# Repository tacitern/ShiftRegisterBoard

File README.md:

# ShiftRegisterBoard
This project uses 8 8bit shift registers to produce 8 data independent bar graphs

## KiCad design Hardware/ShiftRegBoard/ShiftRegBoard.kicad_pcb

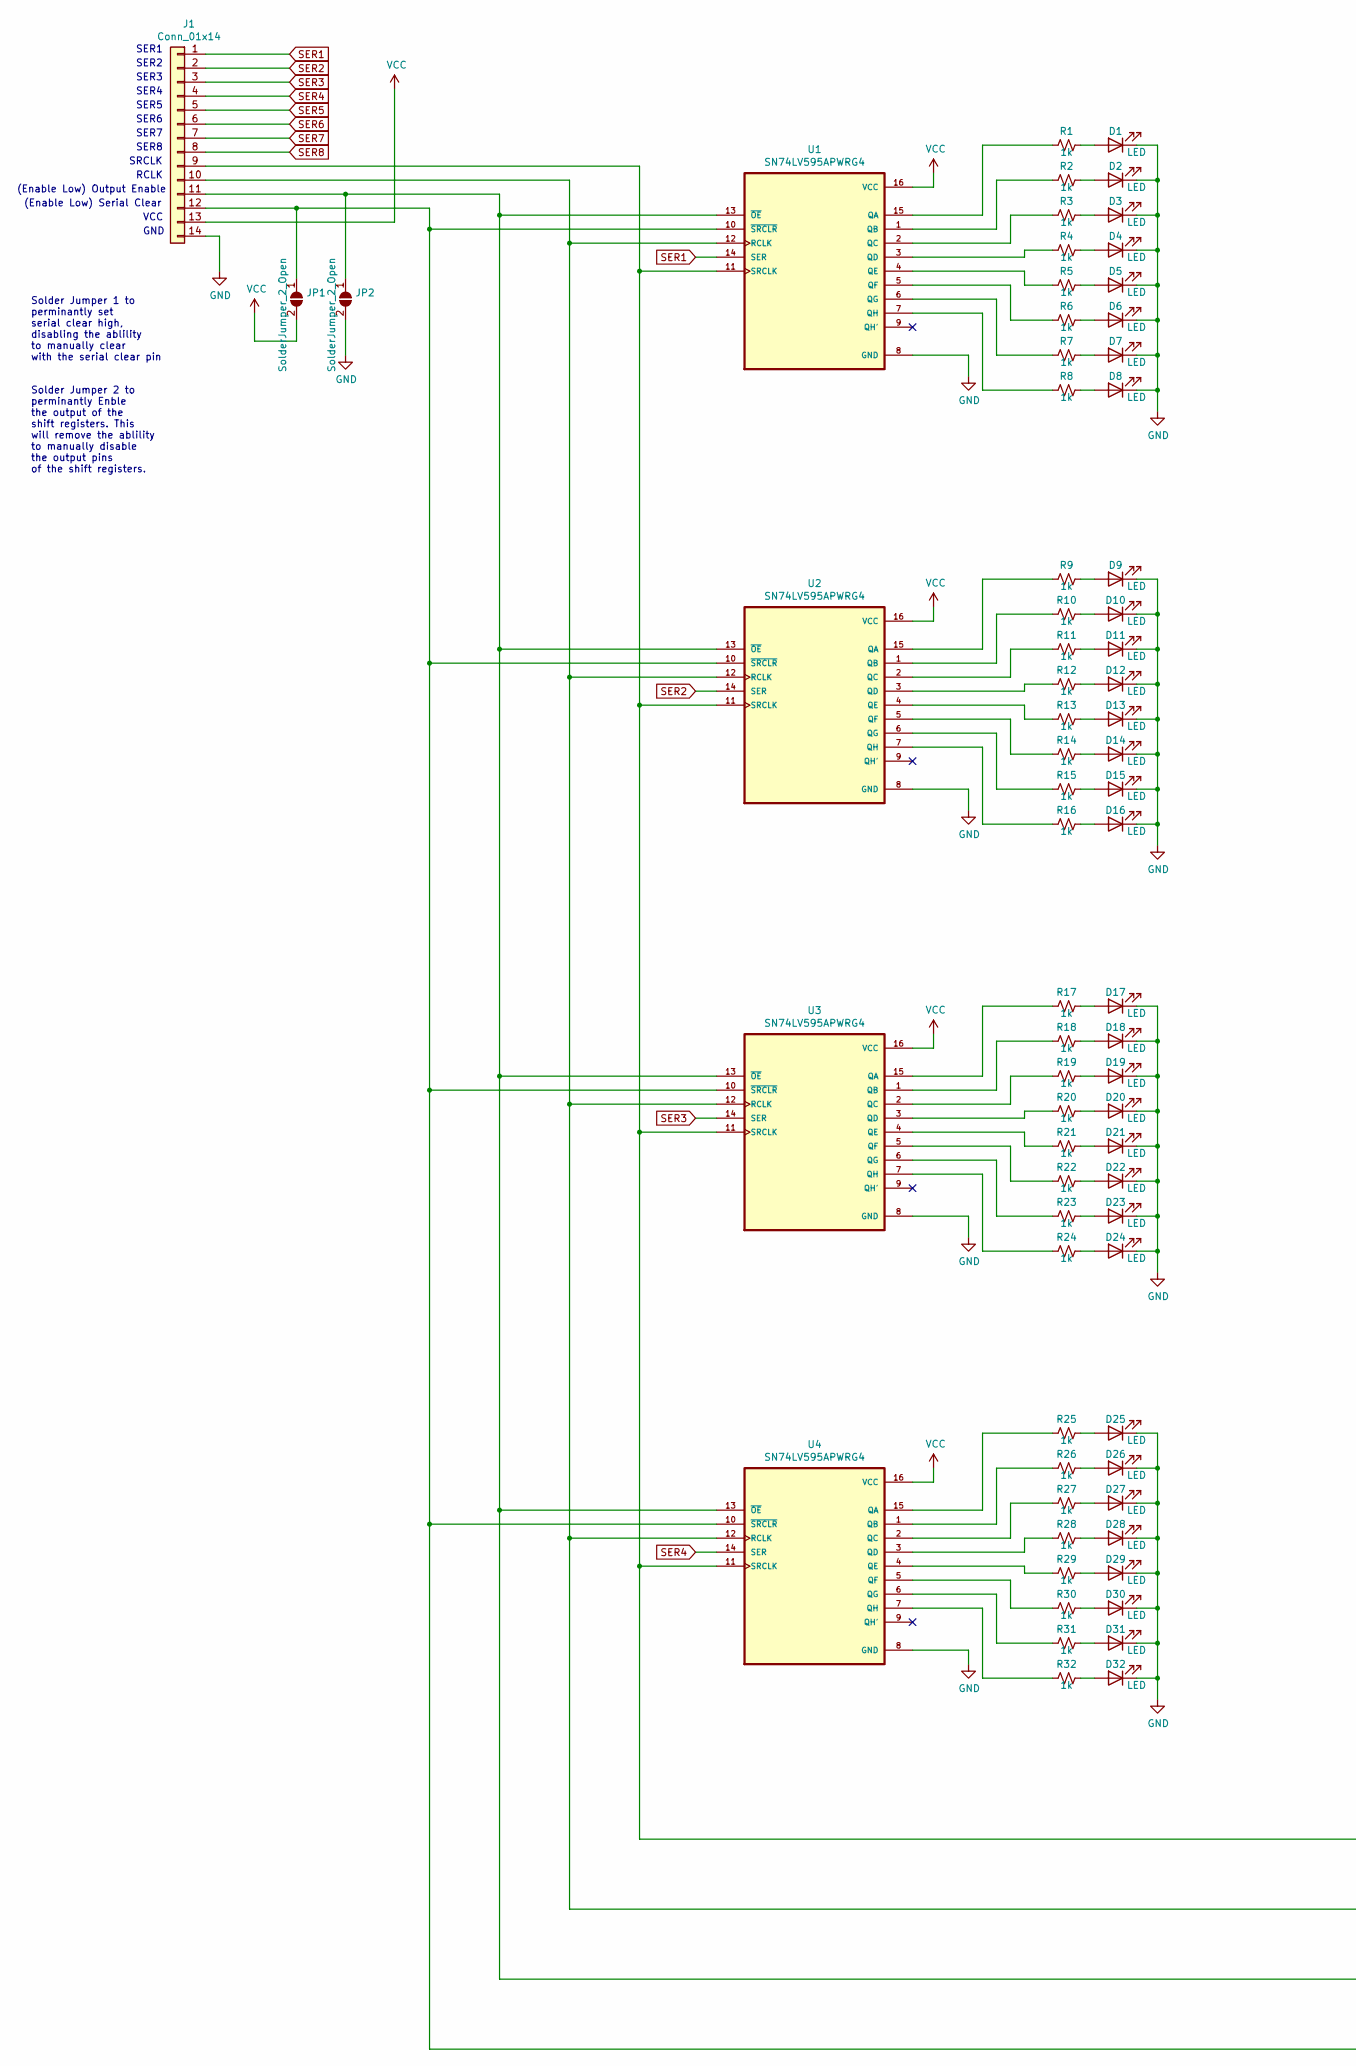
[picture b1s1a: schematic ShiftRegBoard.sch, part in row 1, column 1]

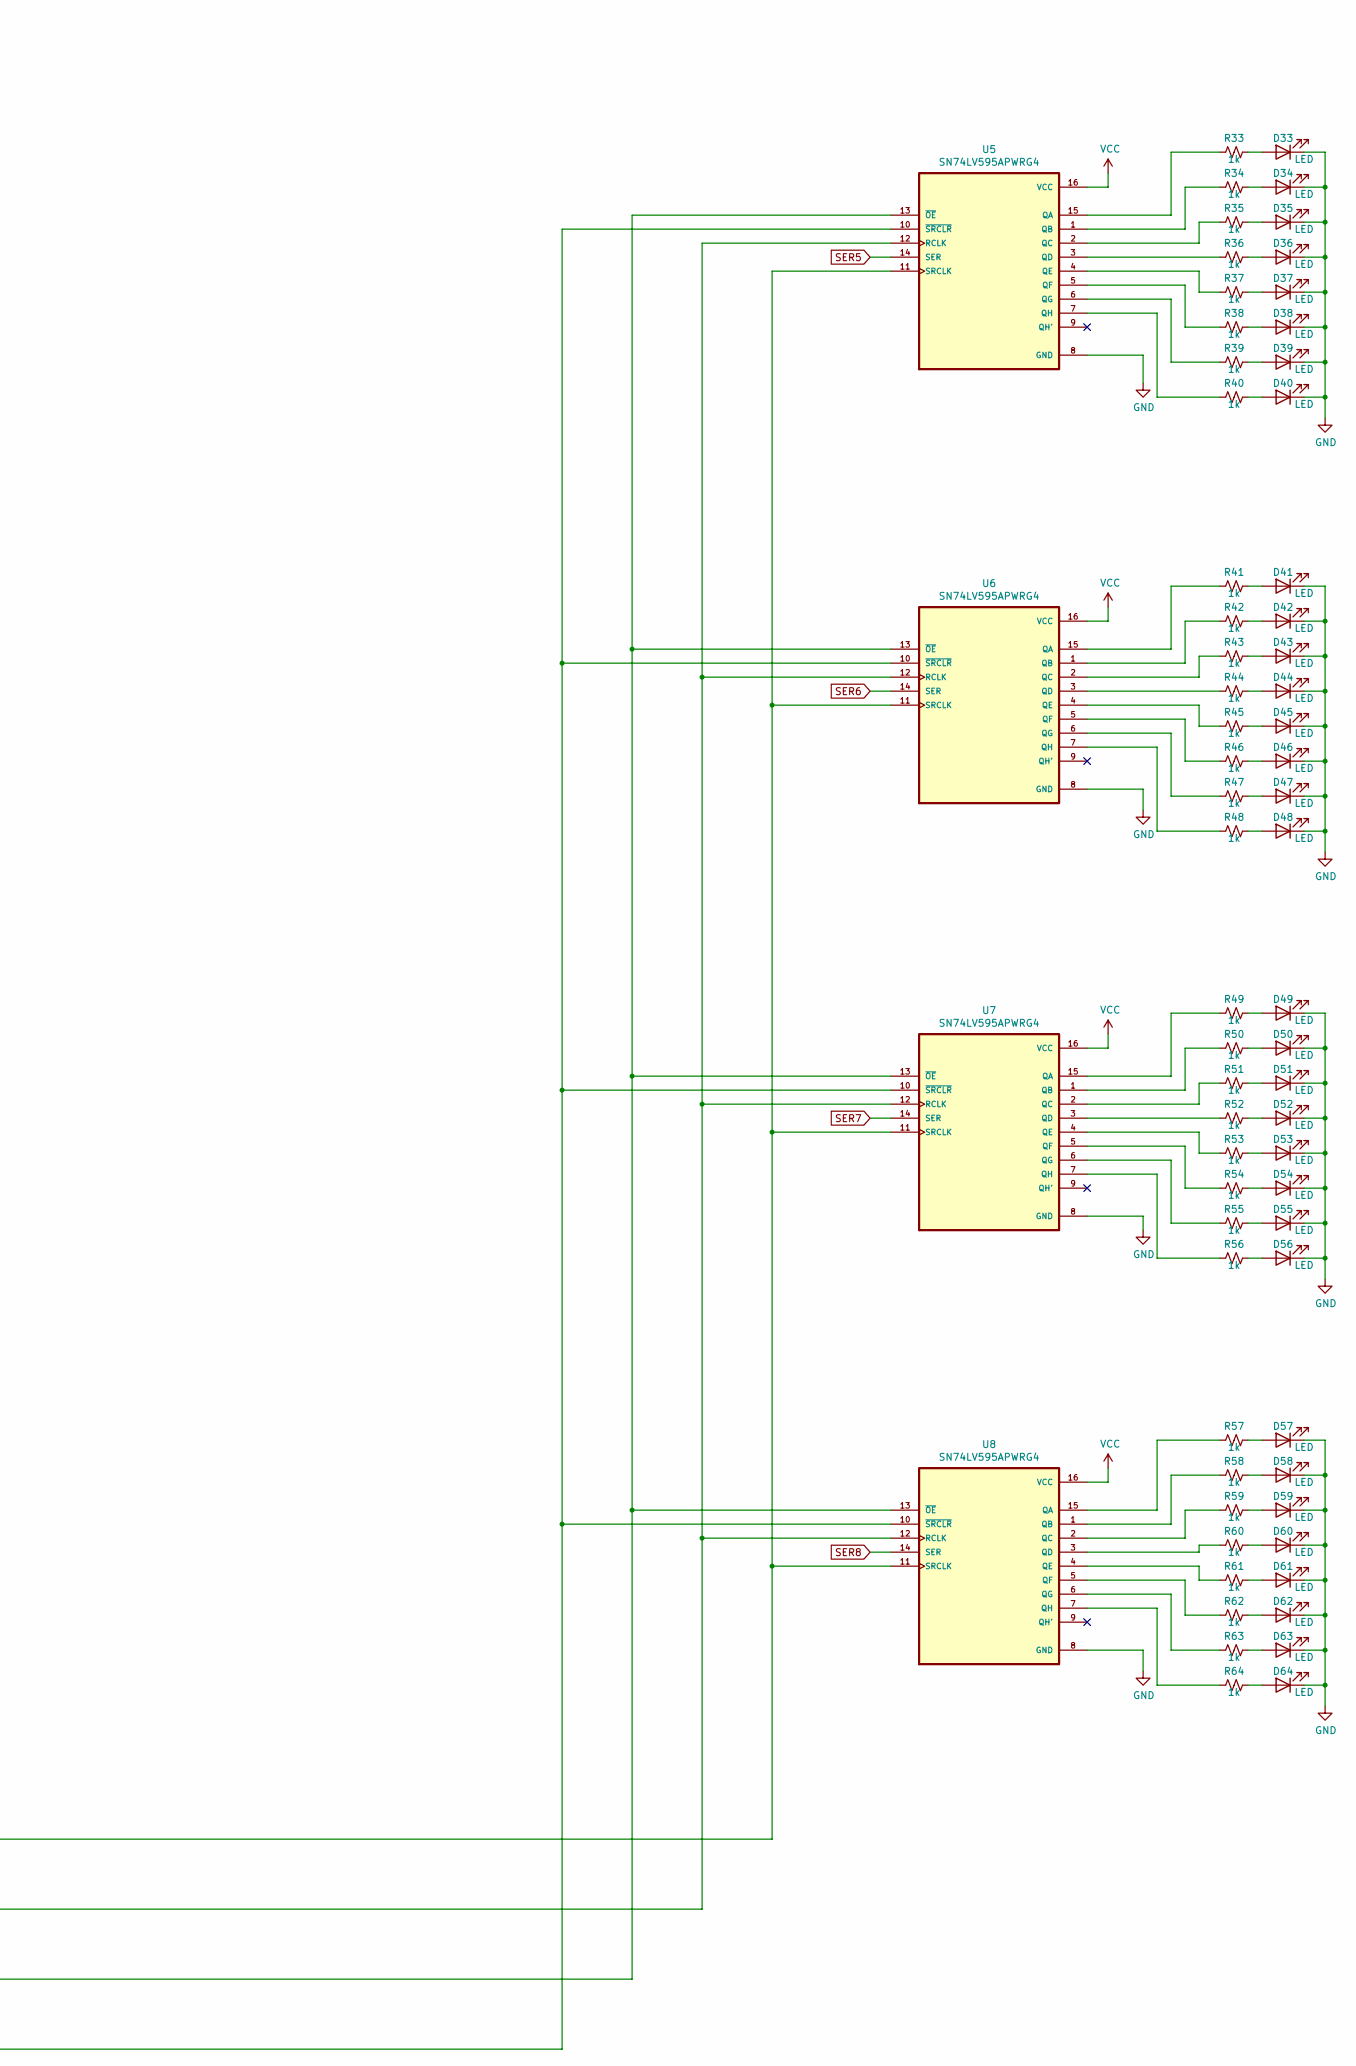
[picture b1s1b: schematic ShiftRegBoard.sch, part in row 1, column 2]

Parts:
D1, D2, D3, D4, D5, D6, D7, D8, D9, D10, D11, D12, D13, D14, D15, D16, D17, D18, D19, D20, D21, D22, D23, D24, D25, D26, D27, D28, D29, D30, D31, D32, D33, D34, D35, D36, D37, D38, D39, D40, D41, D42, D43, D44, D45, D46, D47, D48, D49, D50, D51, D52, D53, D54, D55, D56, D57, D58, D59, D60, D61, D62, D63, D64: LED; LED_0603
J1: Conn_01x14; Pin_Header_Straight_1x14_Pitch2.54mm
JP1, JP2: SolderJumper_2_Open; R_0603
R1, R2, R3, R4, R5, R6, R7, R8, R9, R10, R11, R12, R13, R14, R15, R16, R17, R18, R19, R20, R21, R22, R23, R24, R25, R26, R27, R28, R29, R30, R31, R32, R33, R34, R35, R36, R37, R38, R39, R40, R41, R42, R43, R44, R45, R46, R47, R48, R49, R50, R51, R52, R53, R54, R55, R56, R57, R58, R59, R60, R61, R62, R63, R64: 1k; R_0603
U1, U2, U3, U4, U5, U6, U7, U8: SN74LV595APWRG4; SOP65P640X120-16N

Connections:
GND: D1.1 (K), D2.1 (K), D3.1 (K), D4.1 (K), D5.1 (K), D6.1 (K), D7.1 (K), D8.1 (K), D9.1 (K), D10.1 (K), D11.1 (K), D12.1 (K), D13.1 (K), D14.1 (K), D15.1 (K), D16.1 (K), D17.1 (K), D18.1 (K), D19.1 (K), D20.1 (K), D21.1 (K), D22.1 (K), D23.1 (K), D24.1 (K), D25.1 (K), D26.1 (K), D27.1 (K), D28.1 (K), D29.1 (K), D30.1 (K), D31.1 (K), D32.1 (K), D33.1 (K), D34.1 (K), D35.1 (K), D36.1 (K), D37.1 (K), D38.1 (K), D39.1 (K), D40.1 (K), D41.1 (K), D42.1 (K), D43.1 (K), D44.1 (K), D45.1 (K), D46.1 (K), D47.1 (K), D48.1 (K), D49.1 (K), D50.1 (K), D51.1 (K), D52.1 (K), D53.1 (K), D54.1 (K), D55.1 (K), D56.1 (K), D57.1 (K), D58.1 (K), D59.1 (K), D60.1 (K), D61.1 (K), D62.1 (K), D63.1 (K), D64.1 (K), J1.14, JP2.2 (B), U1.8 (GND), U2.8 (GND), U3.8 (GND), U4.8 (GND), U5.8 (GND), U6.8 (GND), U7.8 (GND), U8.8 (GND)
unnamed: D1.2 (A), R1.1
unnamed: D2.2 (A), R2.1
unnamed: D3.2 (A), R3.1
unnamed: D4.2 (A), R4.1
unnamed: D5.2 (A), R5.1
unnamed: D6.2 (A), R6.1
unnamed: D7.2 (A), R7.1
unnamed: D8.2 (A), R8.1
unnamed: D9.2 (A), R9.1
unnamed: D10.2 (A), R10.1
unnamed: D11.2 (A), R11.1
unnamed: D12.2 (A), R12.1
unnamed: D13.2 (A), R13.1
unnamed: D14.2 (A), R14.1
unnamed: D15.2 (A), R15.1
unnamed: D16.2 (A), R16.1
unnamed: D17.2 (A), R17.1
unnamed: D18.2 (A), R18.1
unnamed: D19.2 (A), R19.1
unnamed: D20.2 (A), R20.1
unnamed: D21.2 (A), R21.1
unnamed: D22.2 (A), R22.1
unnamed: D23.2 (A), R23.1
unnamed: D24.2 (A), R24.1
unnamed: D25.2 (A), R25.1
unnamed: D26.2 (A), R26.1
unnamed: D27.2 (A), R27.1
unnamed: D28.2 (A), R28.1
unnamed: D29.2 (A), R29.1
unnamed: D30.2 (A), R30.1
unnamed: D31.2 (A), R31.1
unnamed: D32.2 (A), R32.1
unnamed: D33.2 (A), R33.1
unnamed: D34.2 (A), R34.1
unnamed: D35.2 (A), R35.1
unnamed: D36.2 (A), R36.1
unnamed: D37.2 (A), R37.1
unnamed: D38.2 (A), R38.1
unnamed: D39.2 (A), R39.1
unnamed: D40.2 (A), R40.1
unnamed: D41.2 (A), R41.1
unnamed: D42.2 (A), R42.1
unnamed: D43.2 (A), R43.1
unnamed: D44.2 (A), R44.1
unnamed: D45.2 (A), R45.1
unnamed: D46.2 (A), R46.1
unnamed: D47.2 (A), R47.1
unnamed: D48.2 (A), R48.1
unnamed: D49.2 (A), R49.1
unnamed: D50.2 (A), R50.1
unnamed: D51.2 (A), R51.1
unnamed: D52.2 (A), R52.1
unnamed: D53.2 (A), R53.1
unnamed: D54.2 (A), R54.1
unnamed: D55.2 (A), R55.1
unnamed: D56.2 (A), R56.1
unnamed: D57.2 (A), R57.1
unnamed: D58.2 (A), R58.1
unnamed: D59.2 (A), R59.1
unnamed: D60.2 (A), R60.1
unnamed: D61.2 (A), R61.1
unnamed: D62.2 (A), R62.1
unnamed: D63.2 (A), R63.1
unnamed: D64.2 (A), R64.1
unnamed: J1.9, U1.11 (SRCLK), U2.11 (SRCLK), U3.11 (SRCLK), U4.11 (SRCLK), U5.11 (SRCLK), U6.11 (SRCLK), U7.11 (SRCLK), U8.11 (SRCLK)
unnamed: J1.10, U1.12 (RCLK), U2.12 (RCLK), U3.12 (RCLK), U4.12 (RCLK), U5.12 (RCLK), U6.12 (RCLK), U7.12 (RCLK), U8.12 (RCLK)
unnamed: J1.11, JP2.1 (A), U1.13 (~OE), U2.13 (~OE), U3.13 (~OE), U4.13 (~OE), U5.13 (~OE), U6.13 (~OE), U7.13 (~OE), U8.13 (~OE)
unnamed: J1.12, JP1.1 (A), U1.10 (~SRCLR), U2.10 (~SRCLR), U3.10 (~SRCLR), U4.10 (~SRCLR), U5.10 (~SRCLR), U6.10 (~SRCLR), U7.10 (~SRCLR), U8.10 (~SRCLR)
unnamed: R1.2, U1.15 (QA)
unnamed: R2.2, U1.1 (QB)
unnamed: R3.2, U1.2 (QC)
unnamed: R4.2, U1.3 (QD)
unnamed: R5.2, U1.4 (QE)
unnamed: R6.2, U1.5 (QF)
unnamed: R7.2, U1.6 (QG)
unnamed: R8.2, U1.7 (QH)
unnamed: R9.2, U2.15 (QA)
unnamed: R10.2, U2.1 (QB)
unnamed: R11.2, U2.2 (QC)
unnamed: R12.2, U2.3 (QD)
unnamed: R13.2, U2.4 (QE)
unnamed: R14.2, U2.5 (QF)
unnamed: R15.2, U2.6 (QG)
unnamed: R16.2, U2.7 (QH)
unnamed: R17.2, U3.15 (QA)
unnamed: R18.2, U3.1 (QB)
unnamed: R19.2, U3.2 (QC)
unnamed: R20.2, U3.3 (QD)
unnamed: R21.2, U3.4 (QE)
unnamed: R22.2, U3.5 (QF)
unnamed: R23.2, U3.6 (QG)
unnamed: R24.2, U3.7 (QH)
unnamed: R25.2, U4.15 (QA)
unnamed: R26.2, U4.1 (QB)
unnamed: R27.2, U4.2 (QC)
unnamed: R28.2, U4.3 (QD)
unnamed: R29.2, U4.4 (QE)
unnamed: R30.2, U4.5 (QF)
unnamed: R31.2, U4.6 (QG)
unnamed: R32.2, U4.7 (QH)
unnamed: R33.2, U5.15 (QA)
unnamed: R34.2, U5.1 (QB)
unnamed: R35.2, U5.2 (QC)
unnamed: R36.2, U5.3 (QD)
unnamed: R37.2, U5.4 (QE)
unnamed: R38.2, U5.5 (QF)
unnamed: R39.2, U5.6 (QG)
unnamed: R40.2, U5.7 (QH)
unnamed: R41.2, U6.15 (QA)
unnamed: R42.2, U6.1 (QB)
unnamed: R43.2, U6.2 (QC)
unnamed: R44.2, U6.3 (QD)
unnamed: R45.2, U6.4 (QE)
unnamed: R46.2, U6.5 (QF)
unnamed: R47.2, U6.6 (QG)
unnamed: R48.2, U6.7 (QH)
unnamed: R49.2, U7.15 (QA)
unnamed: R50.2, U7.1 (QB)
unnamed: R51.2, U7.2 (QC)
unnamed: R52.2, U7.3 (QD)
unnamed: R53.2, U7.4 (QE)
unnamed: R54.2, U7.5 (QF)
unnamed: R55.2, U7.6 (QG)
unnamed: R56.2, U7.7 (QH)
unnamed: R57.2, U8.15 (QA)
unnamed: R58.2, U8.1 (QB)
unnamed: R59.2, U8.2 (QC)
unnamed: R60.2, U8.3 (QD)
unnamed: R61.2, U8.4 (QE)
unnamed: R62.2, U8.5 (QF)
unnamed: R63.2, U8.6 (QG)
unnamed: R64.2, U8.7 (QH)
SER1: J1.1, U1.14 (SER)
SER2: J1.2, U2.14 (SER)
SER3: J1.3, U3.14 (SER)
SER4: J1.4, U4.14 (SER)
SER5: J1.5, U5.14 (SER)
SER6: J1.6, U6.14 (SER)
SER7: J1.7, U7.14 (SER)
SER8: J1.8, U8.14 (SER)
VCC: J1.13, JP1.2 (B), U1.16 (VCC), U2.16 (VCC), U3.16 (VCC), U4.16 (VCC), U5.16 (VCC), U6.16 (VCC), U7.16 (VCC), U8.16 (VCC)

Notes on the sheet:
(Enable Low) Output Enable
(Enable Low) Serial Clear
VCC
GND
RCLK
SRCLK
SER8
SER7
SER6
SER5
SER4
SER3
SER2
SER1
Solder Jumper 1 to perminantly set serial clear high, disabling the ablility to manually clear with the serial clear pin
Solder Jumper 2 to perminantly Enble the output of the shift registers. This will remove the ablility to manually disable the output pins of the shift registers.

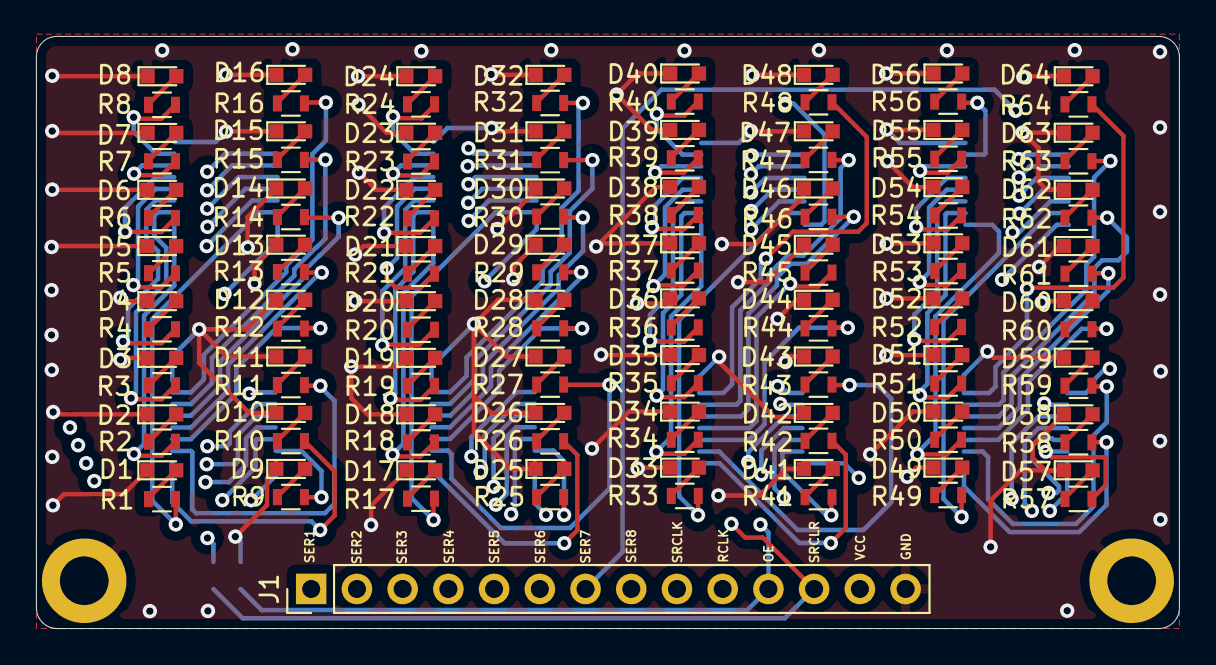
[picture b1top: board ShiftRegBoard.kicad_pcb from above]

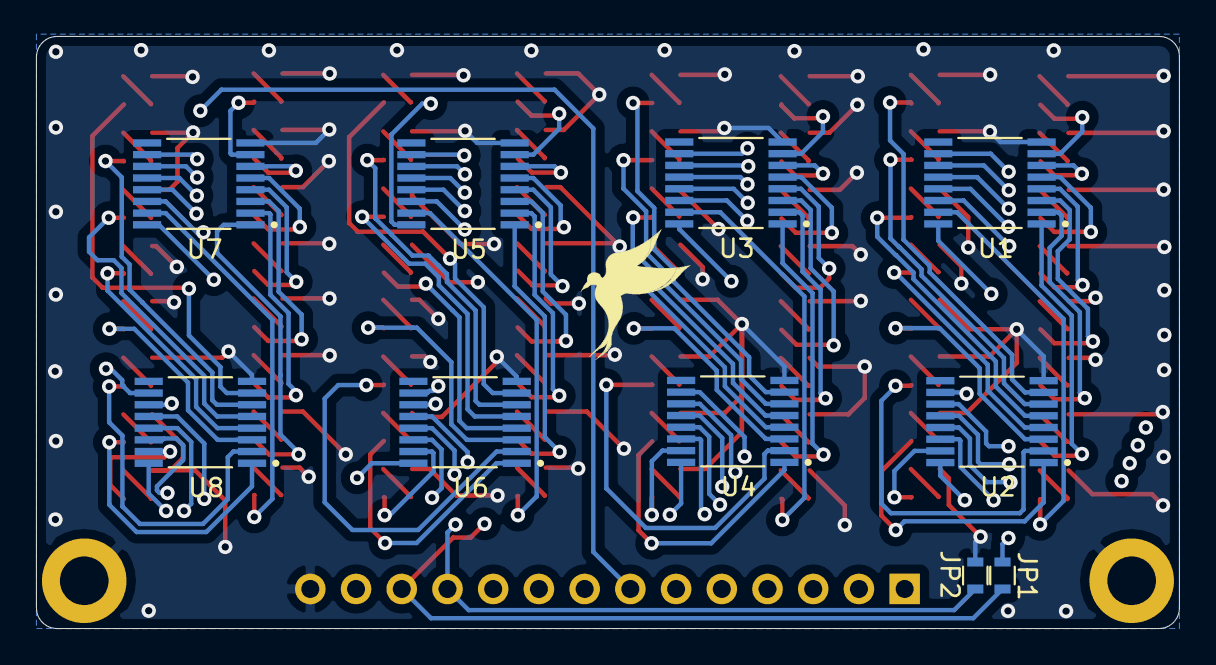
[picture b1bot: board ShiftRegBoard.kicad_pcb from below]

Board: 4 copper layers, 63.5 x 32.9 mm, 139 parts (10 on the bottom side), 142 nets.

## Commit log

2021-09-07 Added Kicad hardware files
2021-12-01 Set theme jekyll-theme-minimal
